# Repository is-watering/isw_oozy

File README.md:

# ISW-OOZY

ISW-OOZY is an orthoish keyboard with offset clusters.

[Build guide](doc/buildguide.md)

## Dependencies (KiCad)
* [is-watering/isw-kbd-lib](https://github.com/is-watering/isw-kbd-lib)
* [Salicylic-acid3/KiCAD_FootPrint](https://github.com/Salicylic-acid3/KiCAD_FootPrint)
* [koktoh/BrownSugar_KBD_KiCad_Library](https://github.com/koktoh/BrownSugar_KBD_KiCad_Library)

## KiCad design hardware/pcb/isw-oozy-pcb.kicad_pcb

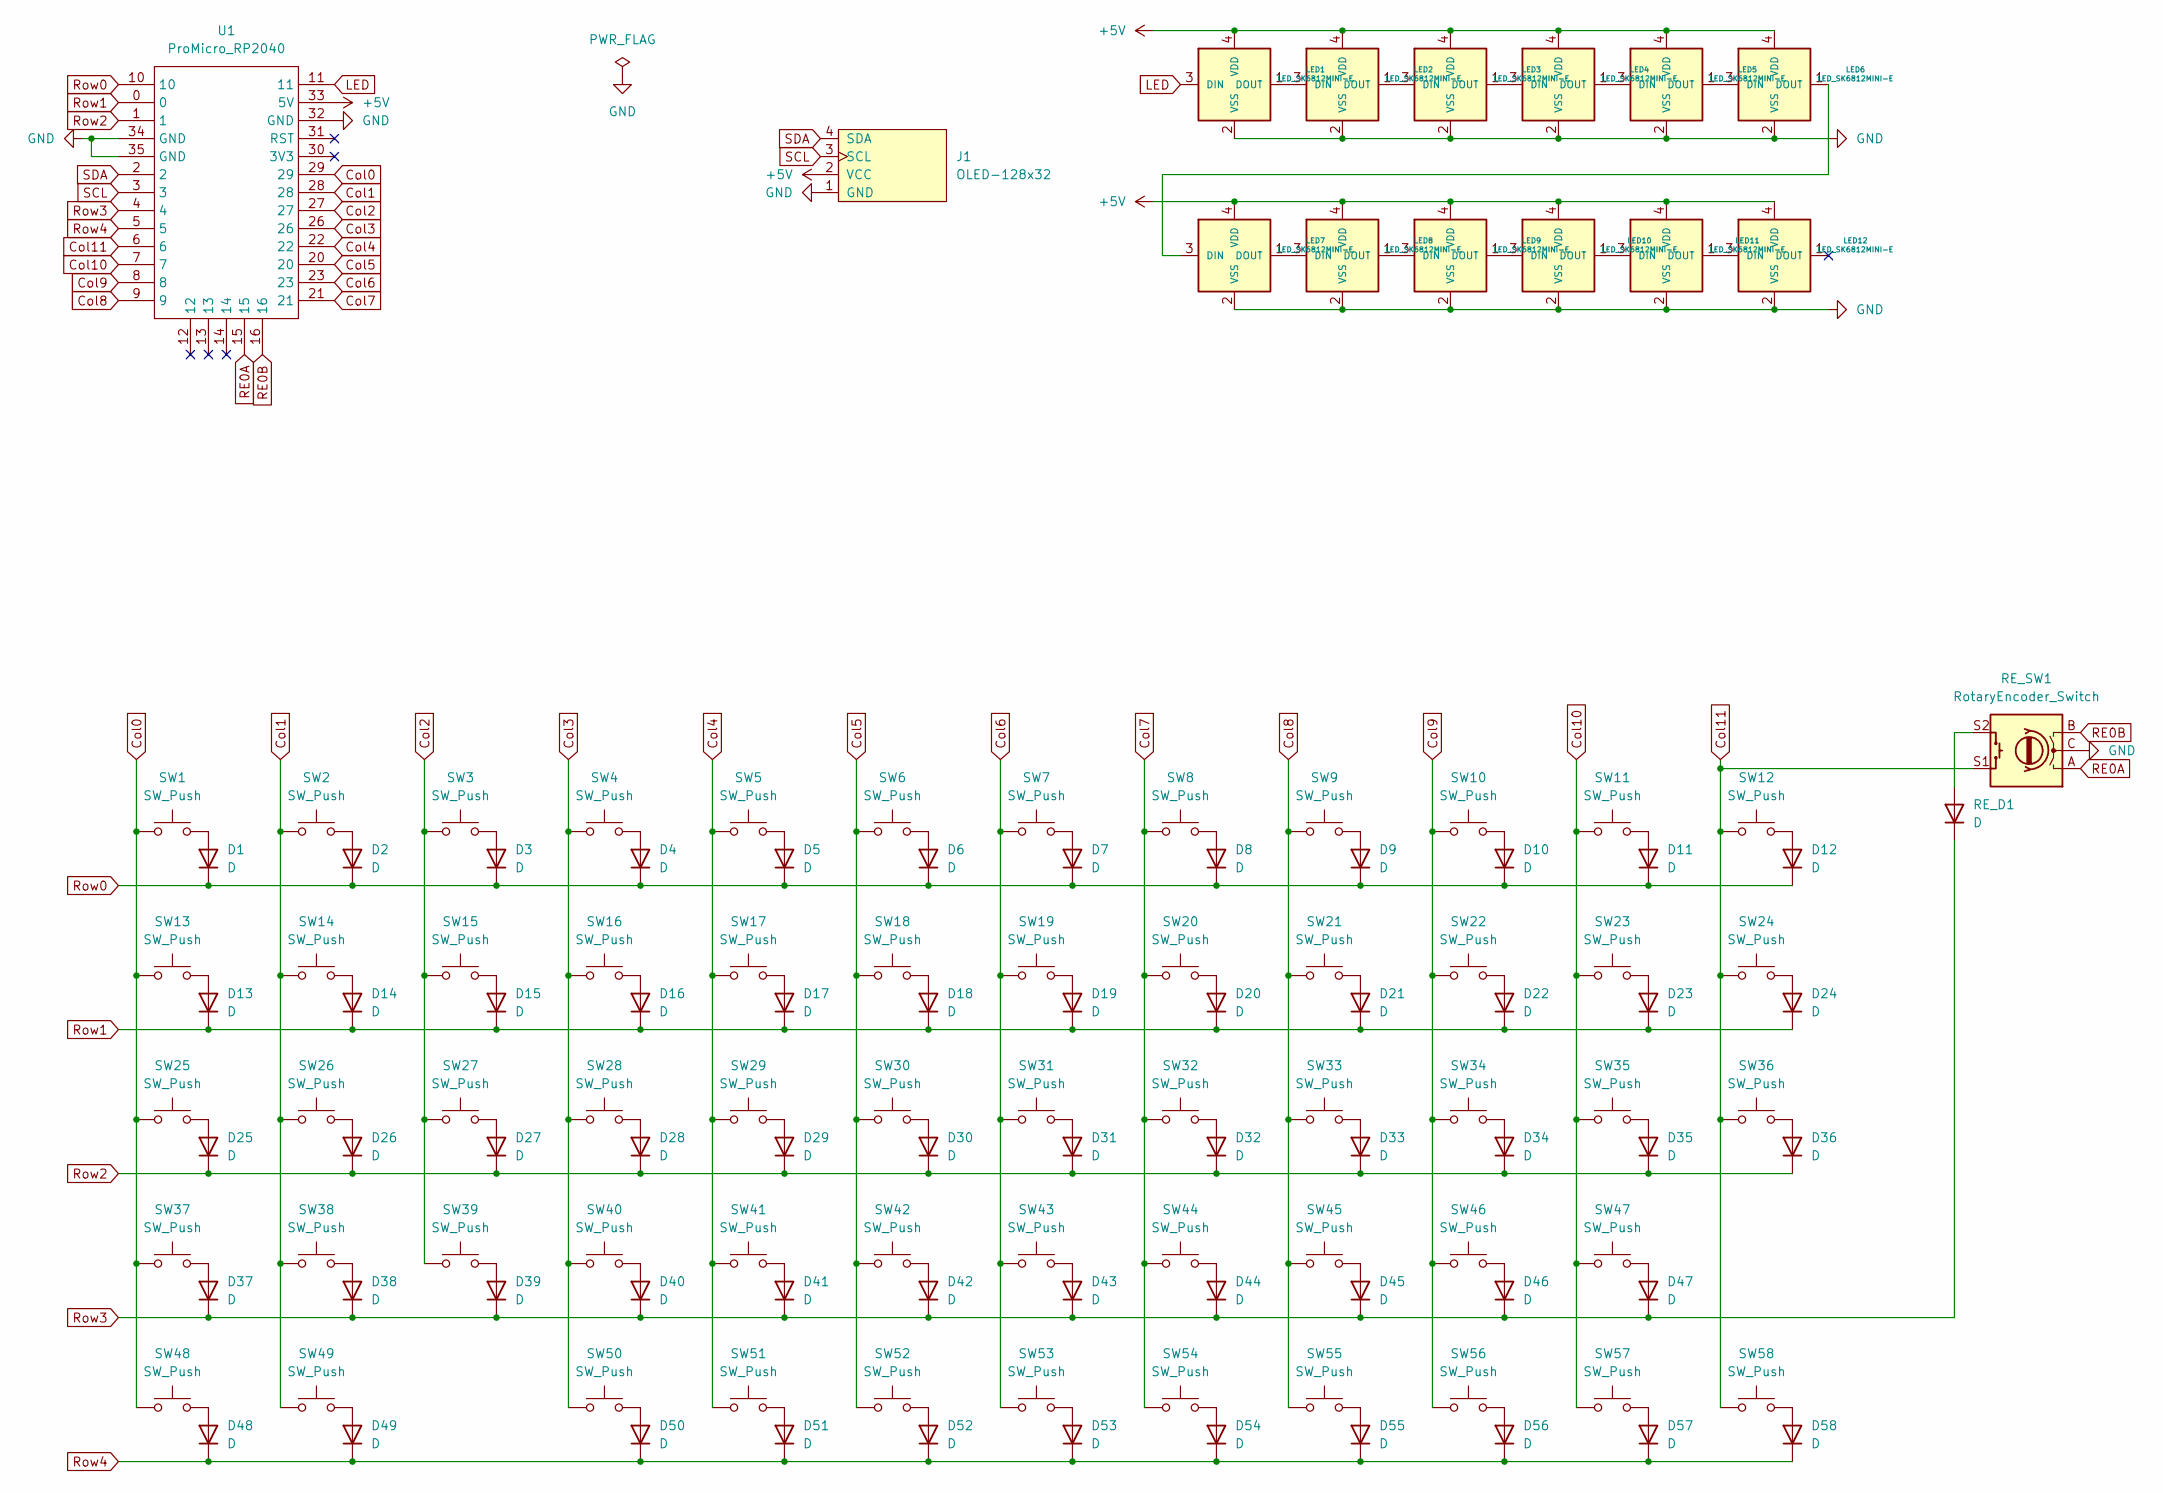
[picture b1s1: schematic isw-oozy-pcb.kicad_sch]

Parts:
D1, D2, D3, D4, D5, D6, D7, D8, D9, D10, D11, D12, D13, D14, D15, D16, D17, D18, D19, D20, D21, D22, D23, D24, D25, D26, D27, D28, D29, D30, D31, D32, D33, D34, D35, D36, D37, D38, D39, D40, D41, D42, D43, D44, D45, D46, D47, D48, D49, D50, D51, D52, D53, D54, D55, D56, D57, D58: D; Diode_TH_SMD
J1: OLED-128x32; AZ1UBALL
LED1, LED2, LED3, LED4, LED5, LED6, LED7, LED8, LED9, LED10, LED11, LED12: LED_SK6812MINI-E; LED_SK6812MINI-E_BL
RE_D1: D; Diode_TH_SMD
RE_SW1: RotaryEncoder_Switch; RotaryEncoder_EVQWGD001
SW1, SW2, SW3, SW4, SW5, SW6, SW7, SW8, SW9, SW10, SW11, SW12, SW13, SW14, SW15, SW16, SW17, SW18, SW19, SW20, SW21, SW22, SW23, SW24, SW25, SW26, SW27, SW28, SW29, SW30, SW31, SW32, SW33, SW34, SW35, SW36, SW37, SW38, SW39, SW40, SW41, SW42, SW43, SW44, SW45, SW46, SW47, SW48, SW49, SW50, SW51, SW52, SW53, SW54, SW55, SW56, SW57, SW58: SW_Push; CherryMX_Hotswap_1u
U1: ProMicro_RP2040

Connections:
+5V: J1.2 (VCC), LED1.4 (VDD), LED2.4 (VDD), LED3.4 (VDD), LED4.4 (VDD), LED5.4 (VDD), LED6.4 (VDD), LED7.4 (VDD), LED8.4 (VDD), LED9.4 (VDD), LED10.4 (VDD), LED11.4 (VDD), LED12.4 (VDD), U1.33 (5V)
Col0: SW1.1, SW13.1, SW25.1, SW37.1, SW48.1, U1.29
Col1: SW2.1, SW14.1, SW26.1, SW38.1, SW49.1, U1.28
Col2: SW3.1, SW15.1, SW27.1, SW39.1, U1.27
Col3: SW4.1, SW16.1, SW28.1, SW40.1, SW50.1, U1.26
Col4: SW5.1, SW17.1, SW29.1, SW41.1, SW51.1, U1.22
Col5: SW6.1, SW18.1, SW30.1, SW42.1, SW52.1, U1.20
Col6: SW7.1, SW19.1, SW31.1, SW43.1, SW53.1, U1.23
Col7: SW8.1, SW20.1, SW32.1, SW44.1, SW54.1, U1.21
Col8: SW9.1, SW21.1, SW33.1, SW45.1, SW55.1, U1.9
Col9: SW10.1, SW22.1, SW34.1, SW46.1, SW56.1, U1.8
Col10: SW11.1, SW23.1, SW35.1, SW47.1, SW57.1, U1.7
Col11: RE_SW1.S1, SW12.1, SW24.1, SW36.1, SW58.1, U1.6
LED: LED1.3 (DIN), U1.11
unnamed: D1.2 (A), SW1.2
unnamed: D2.2 (A), SW2.2
unnamed: D3.2 (A), SW3.2
unnamed: D4.2 (A), SW4.2
unnamed: D5.2 (A), SW5.2
unnamed: D6.2 (A), SW6.2
unnamed: D7.2 (A), SW7.2
unnamed: D8.2 (A), SW8.2
unnamed: D9.2 (A), SW9.2
unnamed: D10.2 (A), SW10.2
unnamed: D11.2 (A), SW11.2
unnamed: D12.2 (A), SW12.2
unnamed: D13.2 (A), SW13.2
unnamed: D14.2 (A), SW14.2
unnamed: D15.2 (A), SW15.2
unnamed: D16.2 (A), SW16.2
unnamed: D17.2 (A), SW17.2
unnamed: D18.2 (A), SW18.2
unnamed: D19.2 (A), SW19.2
unnamed: D20.2 (A), SW20.2
unnamed: D21.2 (A), SW21.2
unnamed: D22.2 (A), SW22.2
unnamed: D23.2 (A), SW23.2
unnamed: D24.2 (A), SW24.2
unnamed: D25.2 (A), SW25.2
unnamed: D26.2 (A), SW26.2
unnamed: D27.2 (A), SW27.2
unnamed: D28.2 (A), SW28.2
unnamed: D29.2 (A), SW29.2
unnamed: D30.2 (A), SW30.2
unnamed: D31.2 (A), SW31.2
unnamed: D32.2 (A), SW32.2
unnamed: D33.2 (A), SW33.2
unnamed: D34.2 (A), SW34.2
unnamed: D35.2 (A), SW35.2
unnamed: D36.2 (A), SW36.2
unnamed: D37.2 (A), SW37.2
unnamed: D38.2 (A), SW38.2
unnamed: D39.2 (A), SW39.2
unnamed: D40.2 (A), SW40.2
unnamed: D41.2 (A), SW41.2
unnamed: D42.2 (A), SW42.2
unnamed: D43.2 (A), SW43.2
unnamed: D44.2 (A), SW44.2
unnamed: D45.2 (A), SW45.2
unnamed: D46.2 (A), SW46.2
unnamed: D47.2 (A), SW47.2
unnamed: D48.2 (A), SW48.2
unnamed: D49.2 (A), SW49.2
unnamed: D50.2 (A), SW50.2
unnamed: D51.2 (A), SW51.2
unnamed: D52.2 (A), SW52.2
unnamed: D53.2 (A), SW53.2
unnamed: D54.2 (A), SW54.2
unnamed: D55.2 (A), SW55.2
unnamed: D56.2 (A), SW56.2
unnamed: D57.2 (A), SW57.2
unnamed: D58.2 (A), SW58.2
unnamed: LED1.1 (DOUT), LED2.3 (DIN)
unnamed: LED2.1 (DOUT), LED3.3 (DIN)
unnamed: LED3.1 (DOUT), LED4.3 (DIN)
unnamed: LED4.1 (DOUT), LED5.3 (DIN)
unnamed: LED5.1 (DOUT), LED6.3 (DIN)
unnamed: LED7.1 (DOUT), LED8.3 (DIN)
unnamed: LED8.1 (DOUT), LED9.3 (DIN)
unnamed: LED9.1 (DOUT), LED10.3 (DIN)
unnamed: LED10.1 (DOUT), LED11.3 (DIN)
unnamed: LED11.1 (DOUT), LED12.3 (DIN)
unnamed: RE_D1.2 (A), RE_SW1.S2
RE0A: RE_SW1.A, U1.15
RE0B: RE_SW1.B, U1.16
Row0: D1.1 (K), D2.1 (K), D3.1 (K), D4.1 (K), D5.1 (K), D6.1 (K), D7.1 (K), D8.1 (K), D9.1 (K), D10.1 (K), D11.1 (K), D12.1 (K), U1.10
Row1: D13.1 (K), D14.1 (K), D15.1 (K), D16.1 (K), D17.1 (K), D18.1 (K), D19.1 (K), D20.1 (K), D21.1 (K), D22.1 (K), D23.1 (K), D24.1 (K), U1.0
Row2: D25.1 (K), D26.1 (K), D27.1 (K), D28.1 (K), D29.1 (K), D30.1 (K), D31.1 (K), D32.1 (K), D33.1 (K), D34.1 (K), D35.1 (K), D36.1 (K), U1.1
Row3: D37.1 (K), D38.1 (K), D39.1 (K), D40.1 (K), D41.1 (K), D42.1 (K), D43.1 (K), D44.1 (K), D45.1 (K), D46.1 (K), D47.1 (K), RE_D1.1 (K), U1.4
Row4: D48.1 (K), D49.1 (K), D50.1 (K), D51.1 (K), D52.1 (K), D53.1 (K), D54.1 (K), D55.1 (K), D56.1 (K), D57.1 (K), D58.1 (K), U1.5
SCL: J1.3 (SCL), U1.3
SDA: J1.4 (SDA), U1.2

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
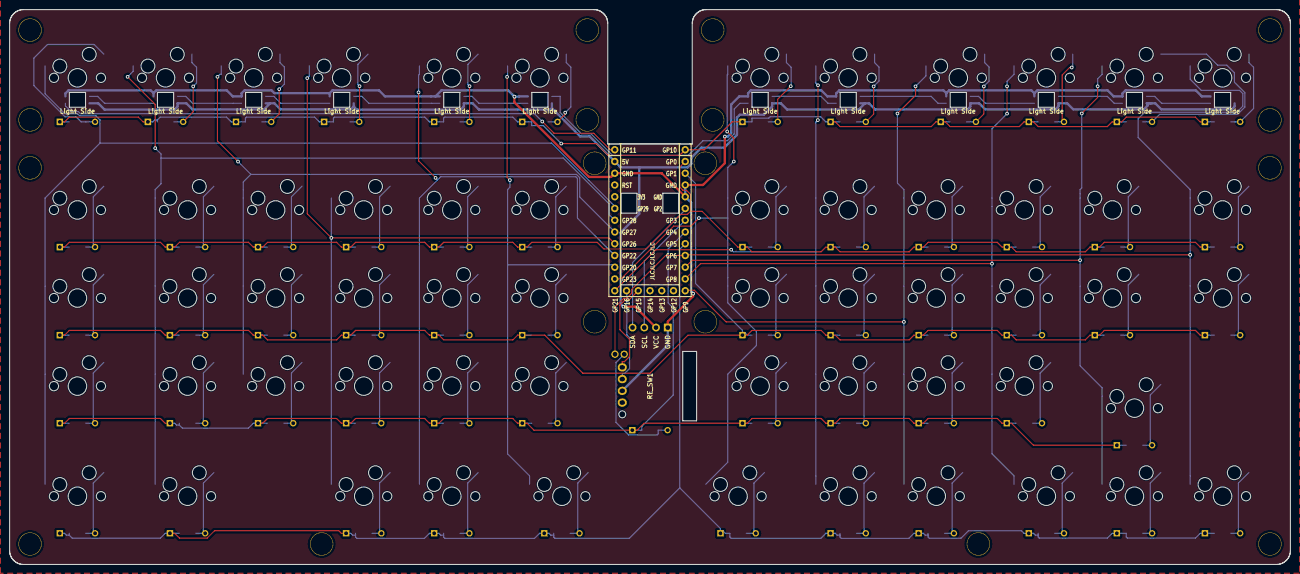
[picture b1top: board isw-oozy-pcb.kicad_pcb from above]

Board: 2 copper layers, 277.0 x 120.0 mm, 150 parts (0 on the bottom side), 94 nets.

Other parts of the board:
Ref01: Val01; m2_Spacer_Hole
Ref02: Val02; m2_Spacer_Hole
Ref03: Val03; m2_Spacer_Hole
Ref04: Val04; m2_Spacer_Hole
Ref05: Val05; m2_Spacer_Hole
Ref06: Val06; m2_Spacer_Hole
Ref07: Val07; m2_Spacer_Hole
Ref08: Val08; m2_Spacer_Hole
Ref09: Val09; m2_Spacer_Hole
Ref10: Val10; m2_Spacer_Hole
Ref11: Val11; m2_Spacer_Hole
Ref12: Val12; m2_Spacer_Hole
Ref13: Val13; m2_Spacer_Hole
Ref14: Val14; m2_Spacer_Hole
Ref15: Val15; m2_Spacer_Hole
Ref16: Val16; m2_Spacer_Hole
Ref17: Val17; m2_Spacer_Hole
Ref18: Val18; m2_Spacer_Hole

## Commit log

2025-07-22 update: firmware
